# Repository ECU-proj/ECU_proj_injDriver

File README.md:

# ECU Project

The injector driver is an integral part of a broader project aimed at creating a fully customizable Engine Control Unit (ECU). The project’s objective is to provide a versatile tool capable of handling everything from straightforward retrofits to professional scenarios where writing custom software tailored to specific applications is essential. Both the hardware and software components are entirely open source and compatible with professional interfaces, representing the cutting edge in the field of engine and vehicle control

## Dual Injector Driver - Alpha Hardware put in production

The injection stage is a fundamental and delicate component of engine control systems. There are two types of injectors:

High Impedance: Usually, Port Fuel Injection (PFI) injectors have a high-impedance solenoid, which automatically limits the current, albeit at the expense of opening speed and precision.
Low Impedance: Typically, newer Gasoline Direct Injection (GDI) injectors require current control and are more sophisticated. A low impedance driver can drive an high impedance injector with simpler software

The driver mainly focus on injectors, while it will used in other applications also, such as GDI pumps actuations, trasmission solenoids, ....

### Injector Driver Hardware

The injector driver hardware is based on the new TI H-Bridge IC DRV8262 controlled by an Attiny 1624
The driver is capable of 70V and 8A peak in dual configuration (two injectors per driver), which is more than enough for the injectors I had experience on.
The board features a high/low voltage switch for correctly implementing the V boost logic. As the supply switch is in common, controlling the voltage on both the injectors in the same time is not possible. Injection number must be carefully assigned in order to avoid control overlap

### Injector Driver Software

Input: logic pulse corresponding to Injection time from ecu
Output: PID control of the current through the injectors

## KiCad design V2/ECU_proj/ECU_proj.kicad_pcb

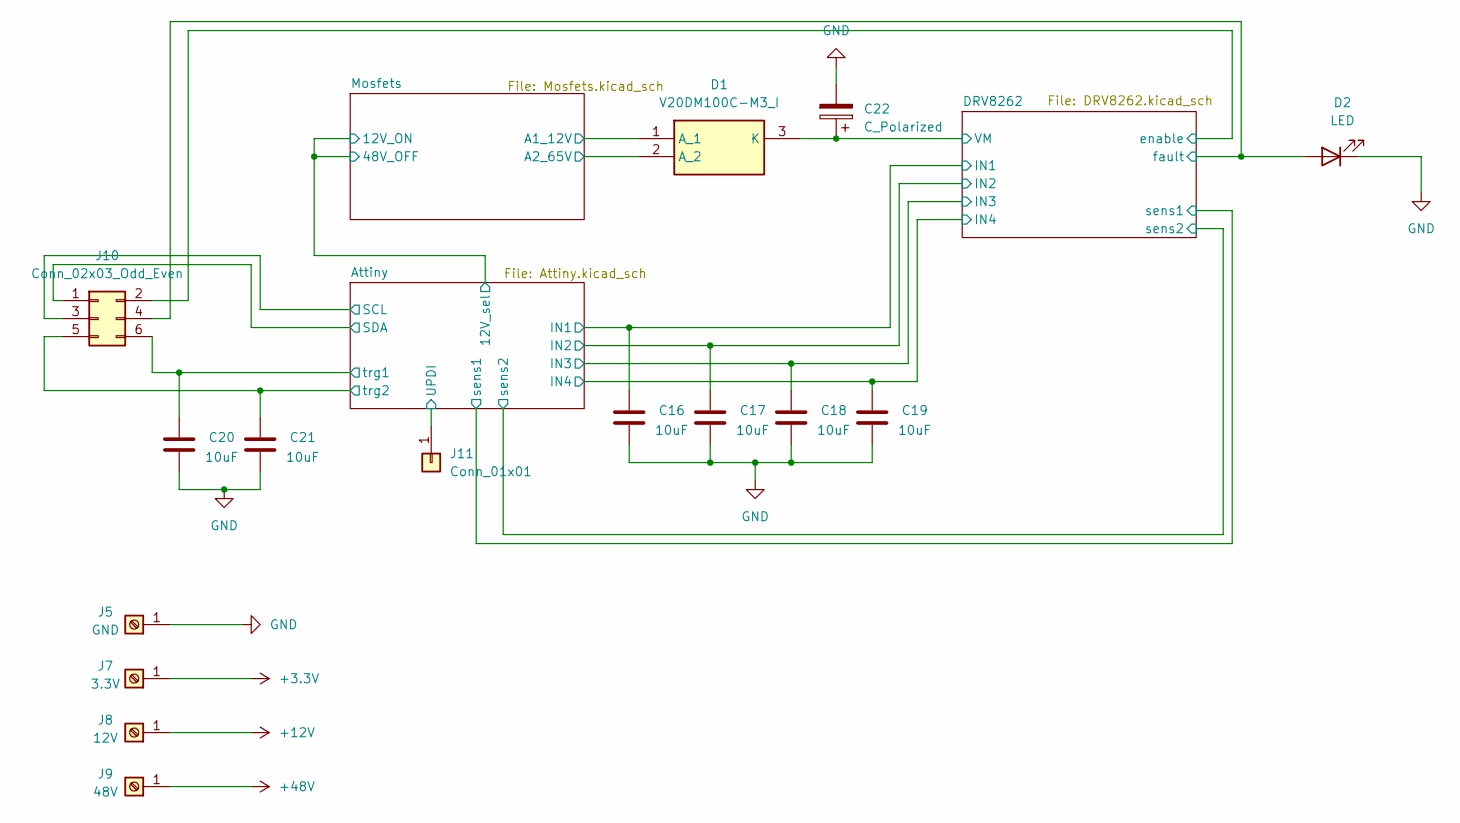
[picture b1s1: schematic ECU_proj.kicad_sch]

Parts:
C16, C17, C18, C19, C20, C21: 10uF; C_0402_1005Metric
C22: C_Polarized; CP_Elec_8x11.9
D1: V20DM100C-M3_I; V20DM100C; Mouser Part Number 78-V20DM100C-M3/I
D2: LED; LED_0402_1005Metric
J5: GND; MountingHole_3.2mm_M3_ISO7380_Pad_TopBottom
J7: 3.3V; MountingHole_3.2mm_M3_ISO7380_Pad_TopBottom
J8: 12V; MountingHole_3.2mm_M3_ISO7380_Pad_TopBottom
J9: 48V; MountingHole_3.2mm_M3_ISO7380_Pad_TopBottom
J10: Conn_02x03_Odd_Even; PinHeader_2x03_P1.27mm_Vertical
J11: Conn_01x01; PinHeader_1x01_P1.00mm_Vertical

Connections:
+3.3V: J7.1; also elsewhere on the board
+12V: J8.1; also elsewhere on the board
+48V: J9.1; also elsewhere on the board
/Attiny/IN1: C16.1; also elsewhere on the board
/Attiny/IN2: C17.1; also elsewhere on the board
/Attiny/IN3: C18.1; also elsewhere on the board
/Attiny/IN4: C19.1; also elsewhere on the board
/Attiny/SCL: J10.3; also elsewhere on the board
/Attiny/SDA: J10.1; also elsewhere on the board
/Attiny/UPDI: J11.1; also elsewhere on the board
/Attiny/trg1: C20.1, J10.6; also elsewhere on the board
/Attiny/trg2: C21.1, J10.5; also elsewhere on the board
/DRV8262/VM: C22.1, D1.3 (K); also elsewhere on the board
/DRV8262/enable: J10.2; also elsewhere on the board
/DRV8262/fault: D2.2 (A), J10.4; also elsewhere on the board
/Mosfets/A1_12V: D1.1 (A_1); also elsewhere on the board
/Mosfets/A2_65V: D1.2 (A_2); also elsewhere on the board
GND: C16.2, C17.2, C18.2, C19.2, C20.2, C21.2, C22.2, D2.1 (K), J5.1; also elsewhere on the board

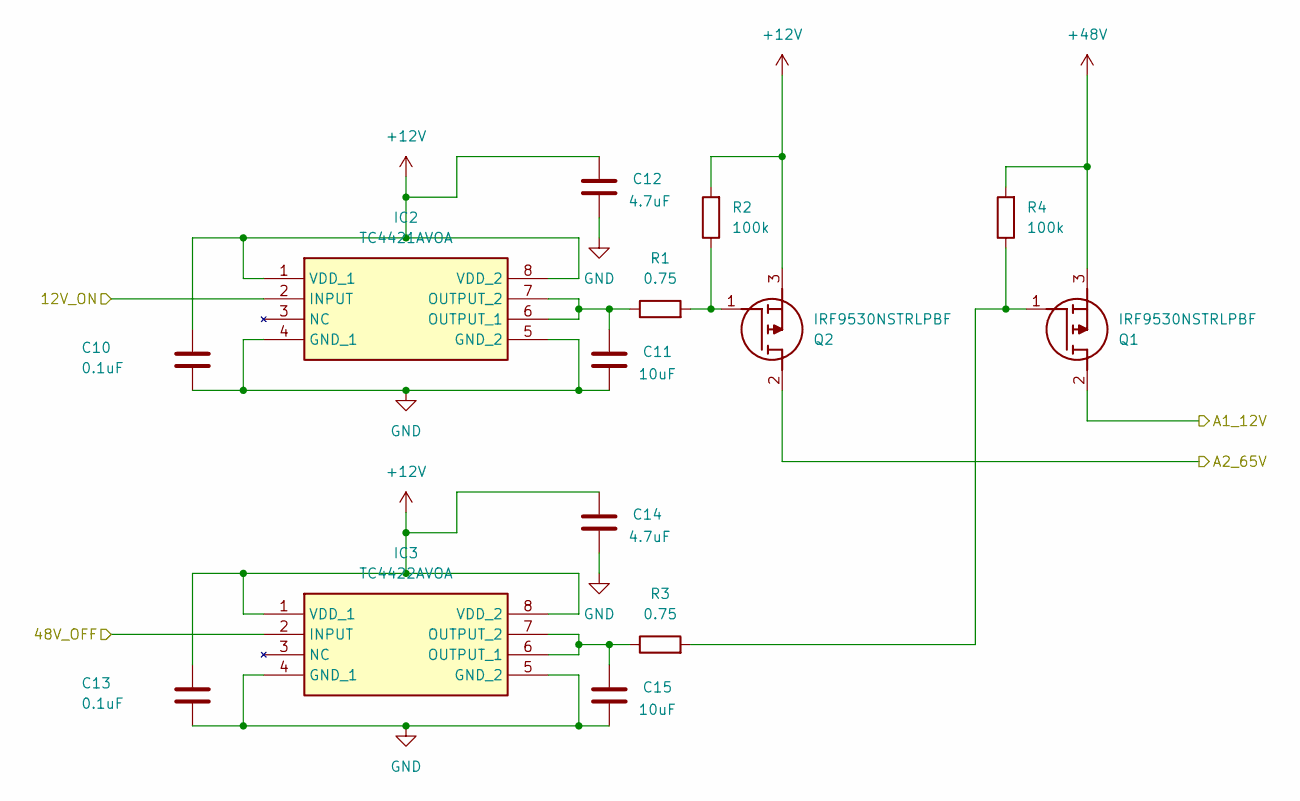
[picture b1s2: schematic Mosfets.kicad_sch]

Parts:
C10, C13: 0.1uF; C_0402_1005Metric
C11, C15: 10uF; C_0402_1005Metric
C12, C14: 4.7uF; C_0402_1005Metric
IC2: TC4421AVOA; TC4422SOIC127P600X175-8N; Mouser Part Number 579-TC4422AVOA
IC3: TC4422AVOA; TC4422SOIC127P600X175-8N; Mouser Part Number 579-TC4422AVOA
Q1, Q2: IRF9530NSTRLPBF; Mouser Part Number 942-IRF9530NSTRLPBF
R1, R3: 0.75; C_0402_1005Metric
R2, R4: 100k; C_0402_1005Metric

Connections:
+12V: C10.1, C12.1, C13.1, C14.1, IC2.1 (VDD_1), IC2.8 (VDD_2), IC3.1 (VDD_1), IC3.8 (VDD_2), Q2.3 (S), R2.2; also elsewhere on the board
+48V: Q1.3 (S), R4.2; also elsewhere on the board
/Attiny/12V_sel: IC2.2 (INPUT), IC3.2 (INPUT); also elsewhere on the board
/Mosfets/A1_12V: Q1.2 (D); also elsewhere on the board
/Mosfets/A2_65V: Q2.2 (D); also elsewhere on the board
GND: C10.2, C11.2, C12.2, C13.2, C14.2, C15.2, IC2.4 (GND_1), IC2.5 (GND_2), IC3.4 (GND_1), IC3.5 (GND_2); also elsewhere on the board
unnamed: C11.1, IC2.6 (OUTPUT_1), IC2.7 (OUTPUT_2), R1.1
unnamed: C15.1, IC3.6 (OUTPUT_1), IC3.7 (OUTPUT_2), R3.1
unnamed: Q1.1 (G), R3.2, R4.1
unnamed: Q2.1 (G), R1.2, R2.1

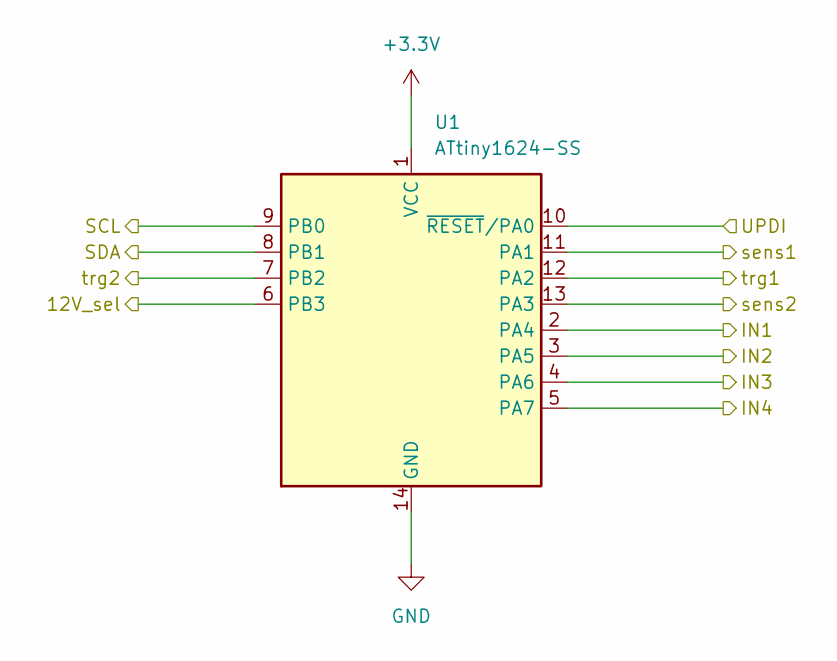
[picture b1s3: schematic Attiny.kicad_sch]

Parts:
U1: ATtiny1624-SS; SOIC-14_3.9x8.7mm_P1.27mm

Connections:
+3.3V: U1.1 (VCC); also elsewhere on the board
/Attiny/12V_sel: U1.6 (PB3); also elsewhere on the board
/Attiny/IN1: U1.2 (PA4); also elsewhere on the board
/Attiny/IN2: U1.3 (PA5); also elsewhere on the board
/Attiny/IN3: U1.4 (PA6); also elsewhere on the board
/Attiny/IN4: U1.5 (PA7); also elsewhere on the board
/Attiny/SCL: U1.9 (PB0); also elsewhere on the board
/Attiny/SDA: U1.8 (PB1); also elsewhere on the board
/Attiny/UPDI: U1.10 (~RESET/PA0); also elsewhere on the board
/Attiny/sens1: U1.11 (PA1); also elsewhere on the board
/Attiny/sens2: U1.13 (PA3); also elsewhere on the board
/Attiny/trg1: U1.12 (PA2); also elsewhere on the board
/Attiny/trg2: U1.7 (PB2); also elsewhere on the board
GND: U1.14 (GND); also elsewhere on the board

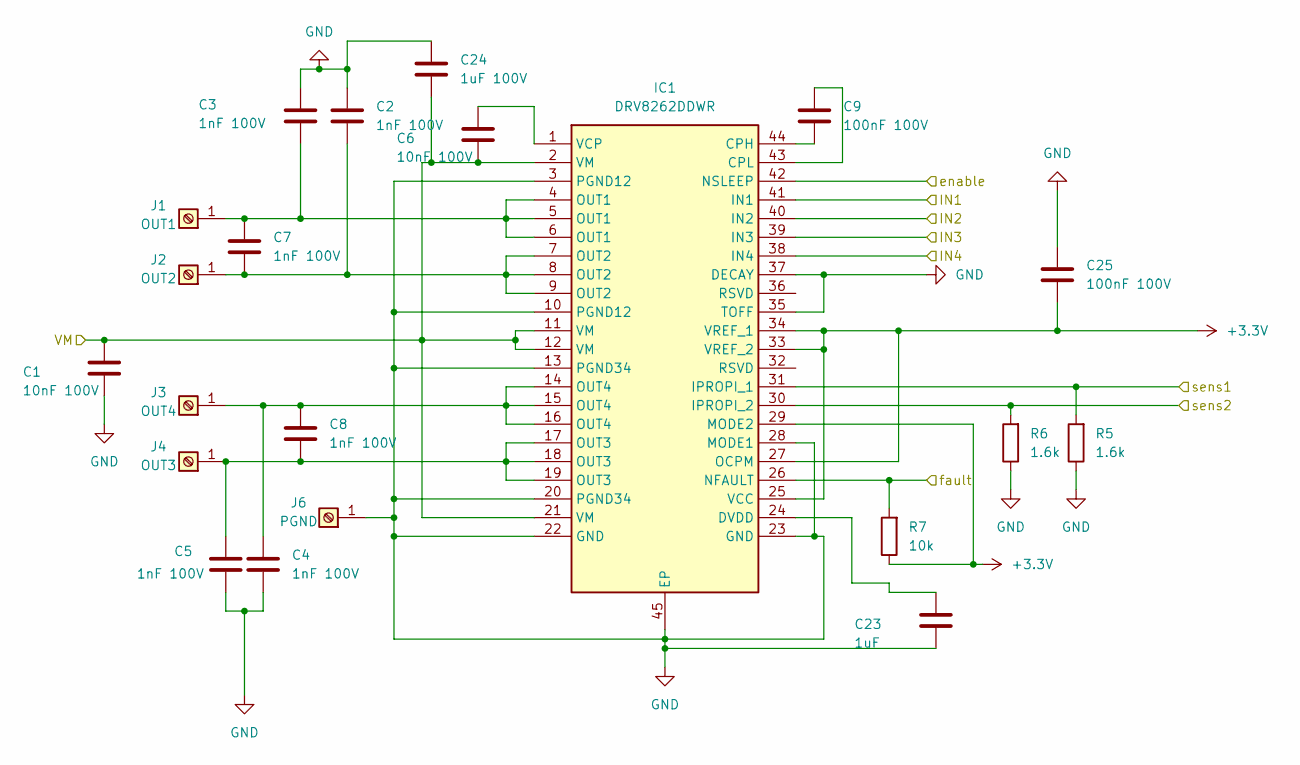
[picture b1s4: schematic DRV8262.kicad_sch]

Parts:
C1, C6: 10nF 100V; C_0402_1005Metric
C2, C3, C4, C5, C7, C8: 1nF 100V; C_0402_1005Metric
C9, C25: 100nF 100V; C_0402_1005Metric
C23: 1uF; C_0402_1005Metric
C24: 1uF 100V; C_0402_1005Metric
IC1: DRV8262DDWR; DRV8262; Mouser Part Number 595-DRV8262DDWR
J1: OUT1; MountingHole_3.2mm_M3_ISO7380_Pad_TopBottom
J2: OUT2; MountingHole_3.2mm_M3_ISO7380_Pad_TopBottom
J3: OUT4; MountingHole_3.2mm_M3_ISO7380_Pad_TopBottom
J4: OUT3; MountingHole_3.2mm_M3_ISO7380_Pad_TopBottom
J6: PGND; MountingHole_3.2mm_M3_ISO7380_Pad_TopBottom
R5, R6: 1.6k; C_0402_1005Metric
R7: 10k; C_0402_1005Metric

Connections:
+3.3V: C25.2, IC1.25 (VCC), IC1.27 (OCPM), IC1.29 (MODE2), IC1.33 (VREF_2), IC1.34 (VREF_1), R7.1; also elsewhere on the board
/Attiny/IN1: IC1.41 (IN1); also elsewhere on the board
/Attiny/IN2: IC1.40 (IN2); also elsewhere on the board
/Attiny/IN3: IC1.39 (IN3); also elsewhere on the board
/Attiny/IN4: IC1.38 (IN4); also elsewhere on the board
/Attiny/sens1: IC1.31 (IPROPI_1), R5.2; also elsewhere on the board
/Attiny/sens2: IC1.30 (IPROPI_2), R6.2; also elsewhere on the board
/DRV8262/VM: C1.1, C6.2, C24.2, IC1.2 (VM), IC1.11 (VM), IC1.12 (VM), IC1.21 (VM); also elsewhere on the board
/DRV8262/enable: IC1.42 (NSLEEP); also elsewhere on the board
/DRV8262/fault: IC1.26 (NFAULT), R7.2; also elsewhere on the board
GND: C1.2, C2.1, C3.1, C4.2, C5.2, C23.2, C24.1, C25.1, IC1.3 (PGND12), IC1.10 (PGND12), IC1.13 (PGND34), IC1.20 (PGND34), IC1.22 (GND), IC1.23 (GND), IC1.28 (MODE1), IC1.35 (TOFF), IC1.37 (DECAY), IC1.45 (EP), J6.1, R5.1, R6.1; also elsewhere on the board
unnamed: C9.2, IC1.44 (CPH)
unnamed: C9.1, IC1.43 (CPL)
unnamed: C23.1, IC1.24 (DVDD)
unnamed: C6.1, IC1.1 (VCP)
unnamed: C3.2, C7.1, IC1.4 (OUT1), IC1.5 (OUT1), IC1.6 (OUT1), J1.1
unnamed: C2.2, C7.2, IC1.7 (OUT2), IC1.8 (OUT2), IC1.9 (OUT2), J2.1
unnamed: C4.1, C8.1, IC1.14 (OUT4), IC1.15 (OUT4), IC1.16 (OUT4), J3.1
unnamed: C5.1, C8.2, IC1.17 (OUT3), IC1.18 (OUT3), IC1.19 (OUT3), J4.1

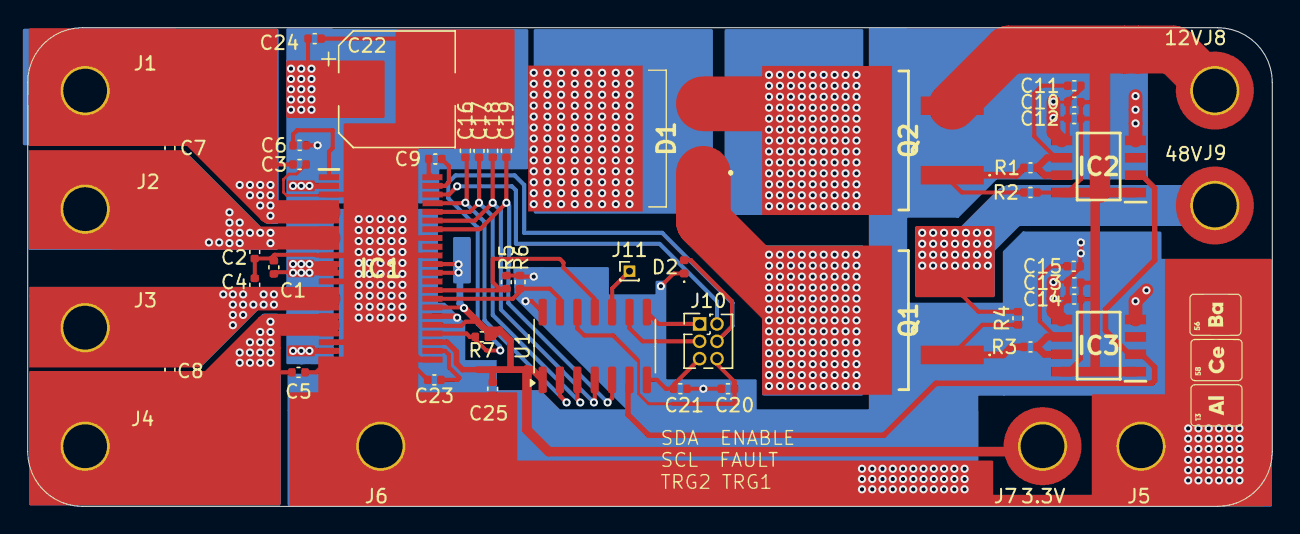
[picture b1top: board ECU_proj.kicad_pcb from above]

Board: 2 copper layers, 91.0 x 35.0 mm, 51 parts (0 on the bottom side), 33 nets.

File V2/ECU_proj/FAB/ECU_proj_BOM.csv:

"Id";"Riferimento";"Impronta";"Quantità";"Valore";"Produttore";
1;"J1";"MountingHole_3.2mm_M3_ISO7380_Pad_TopBottom";1;"OUT1";;;
2;"C12,C14";"C_0402_1005Metric";2;"4.7uF";;;
3;"Q1,Q2";"IRF9530NSTRLPBF";2;"IRF9530NSTRLPBF";;;
4;"C13,C10";"C_0402_1005Metric";2;"0.1uF";;;
5;"J9";"MountingHole_3.2mm_M3_ISO7380_Pad_TopBottom";1;"48V";;;
6;"U1";"SOIC-14_3.9x8.7mm_P1.27mm";1;"ATtiny1624-SS";;;
7;"C23";"C_0402_1005Metric";1;"1uF";;;
8;"C17,C11,C20,C15,C16,C19,C18,C21";"C_0402_1005Metric";8;"10uF";;;
9;"R6,R5";"C_0402_1005Metric";2;"1.6k";;;
10;"J10";"PinHeader_2x03_P1.27mm_Vertical";1;"Conn_02x03_Odd_Even";;;
11;"D2";"LED_0402_1005Metric";1;"LED";;;
12;"C5,C8,C3,C7,C4,C2";"C_0402_1005Metric";6;"1nF 100V";;;
13;"J2";"MountingHole_3.2mm_M3_ISO7380_Pad_TopBottom";1;"OUT2";;;
14;"J5";"MountingHole_3.2mm_M3_ISO7380_Pad_TopBottom";1;"GND";;;
15;"J7";"MountingHole_3.2mm_M3_ISO7380_Pad_TopBottom";1;"3.3V";;;
16;"C1,C6";"C_0402_1005Metric";2;"10nF 100V";;;
17;"IC2";"TC4422SOIC127P600X175-8N";1;"TC4421AVOA";;;
18;"C22";"CP_Elec_8x11.9";1;"C_Polarized";;;
19;"J3";"MountingHole_3.2mm_M3_ISO7380_Pad_TopBottom";1;"OUT4";;;
20;"C9,C25";"C_0402_1005Metric";2;"100nF 100V";;;
21;"C24";"C_0402_1005Metric";1;"1uF 100V";;;
22;"J4";"MountingHole_3.2mm_M3_ISO7380_Pad_TopBottom";1;"OUT3";;;
23;"D1";"V20DM100C";1;"V20DM100C-M3_I";;;
24;"J8";"MountingHole_3.2mm_M3_ISO7380_Pad_TopBottom";1;"12V";;;
25;"R3,R1";"C_0402_1005Metric";2;"0.75";;;
26;"IC1";"DRV8262";1;"DRV8262DDWR";;;
27;"IC3";"TC4422SOIC127P600X175-8N";1;"TC4422AVOA";;;
28;"J11";"PinHeader_1x01_P1.00mm_Vertical";1;"Conn_01x01";;;
29;"J6";"MountingHole_3.2mm_M3_ISO7380_Pad_TopBottom";1;"PGND";;;
30;"R2,R4";"C_0402_1005Metric";2;"100k";;;
31;"R7";"C_0402_1005Metric";1;"10k";;;

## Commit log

2024-04-28 First Release
2024-04-29 Review before PCB production
2024-04-30 Alpha Release
